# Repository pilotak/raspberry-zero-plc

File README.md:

# Raspberry Pi Zero/W based PLC
DIN mount PLC with following features
- power supply 7-45V DC
- 2x SPDT relay
- 1x SSR relay output (positive)
- 4x mosfet output (negative)
- 4x opto-isolated digital inputs with hardware debounce
- 3x analog input + 1 additional for power supply monitoring
- 1x CAN interface
- 1x RS232 (can be used for console or as standalone serial port)

## Picture

## BOM

| Qty | Component | Value | Package |
|:---:| --------- | ----- | ------- |
| 4 | Capacitor | 1uF/6.3V | C0805 |
| 2 | Capacitor | 10uF/6.3V | C0805 |
| 2 | Capacitor | 22p | C0805 |
| 12 | Capacitor | 100n | C0805 |
| 1 | Capacitor | 100uF/50V | PANASONIC_E |
| 1 | Capacitor | 470uF/10V | PANASONIC_E |
| 6 | Diode | S1B | DO214AC (SMA) |
| 1 | TVS | SMBJ33 | DO214AA (SMB) |
| 2 | Shottky diode| SS26 | DO214AA (SMB) |
| 1 | NAND Schmitt trigger | 74HC132D | SO14 |
| 1 | CAN controller | MCP2515-I/SO | SO-18L |
| 1 | RS232 driver | SP3222EET | SO-18L |
| 1 | CAN transceiver | TJA1050 | SO08 |
| 4 | Photocoupler | TLP185 | SOP04 |
| 1 | SSR relay | AQY212S | SOP04 |
| 2 | Realy | SRD-5VDC-SL-C | |
| 1 | Inductor | DE1207-100 | DR125 |
| 4 | N-mosfet | 2N7002 | SOT23 |
| 1 | Crystal | 16MHz | HC49U-V |
| 2 | PNP transistor | BCX71SMD | SOT23 |
| 1 | P-mosfet | DMG2305UX | SOT23 |
| 2 | N-mosfet | IRLML0060TRPBF | SOT23 |
| 5 | Resistor| 1K | R0805 |
| 5 | Resistor| 2K2 | R0805 |
| 4 | Resistor| 10K | R0805 |
| 1 | Resistor| 18K | R0805 |
| 3 | Resistor| 47K | R0805 |
| 4 | Resistor| 68K | R0805 |
| 6 | Resistor| 100K | R0805 |
| 1 | Resistor| 120R | R1206 |
| 4 | Resistor| 820K | R0805 |
| 1 | ADC | ADS1015 | module |
| 1 | LDO regulator | LM1117-3.3 | SOT223 |
| 1 | Step-down regulator | LM2576-5.0 | TO-263-5 |
| 1 | Raspberry Pi | Zero | |
| 2 | Screw terminal| KF301-5.0-2P | KF301-5.0-2P |
| 2 | Screw terminal| KF301-5.0-3P | KF301-5.0-3P |
| 7 | Screw terminal| KF350-3.5-2P | KF350-3.50-2P |
| 1 | DIN case | Z100J PS | |

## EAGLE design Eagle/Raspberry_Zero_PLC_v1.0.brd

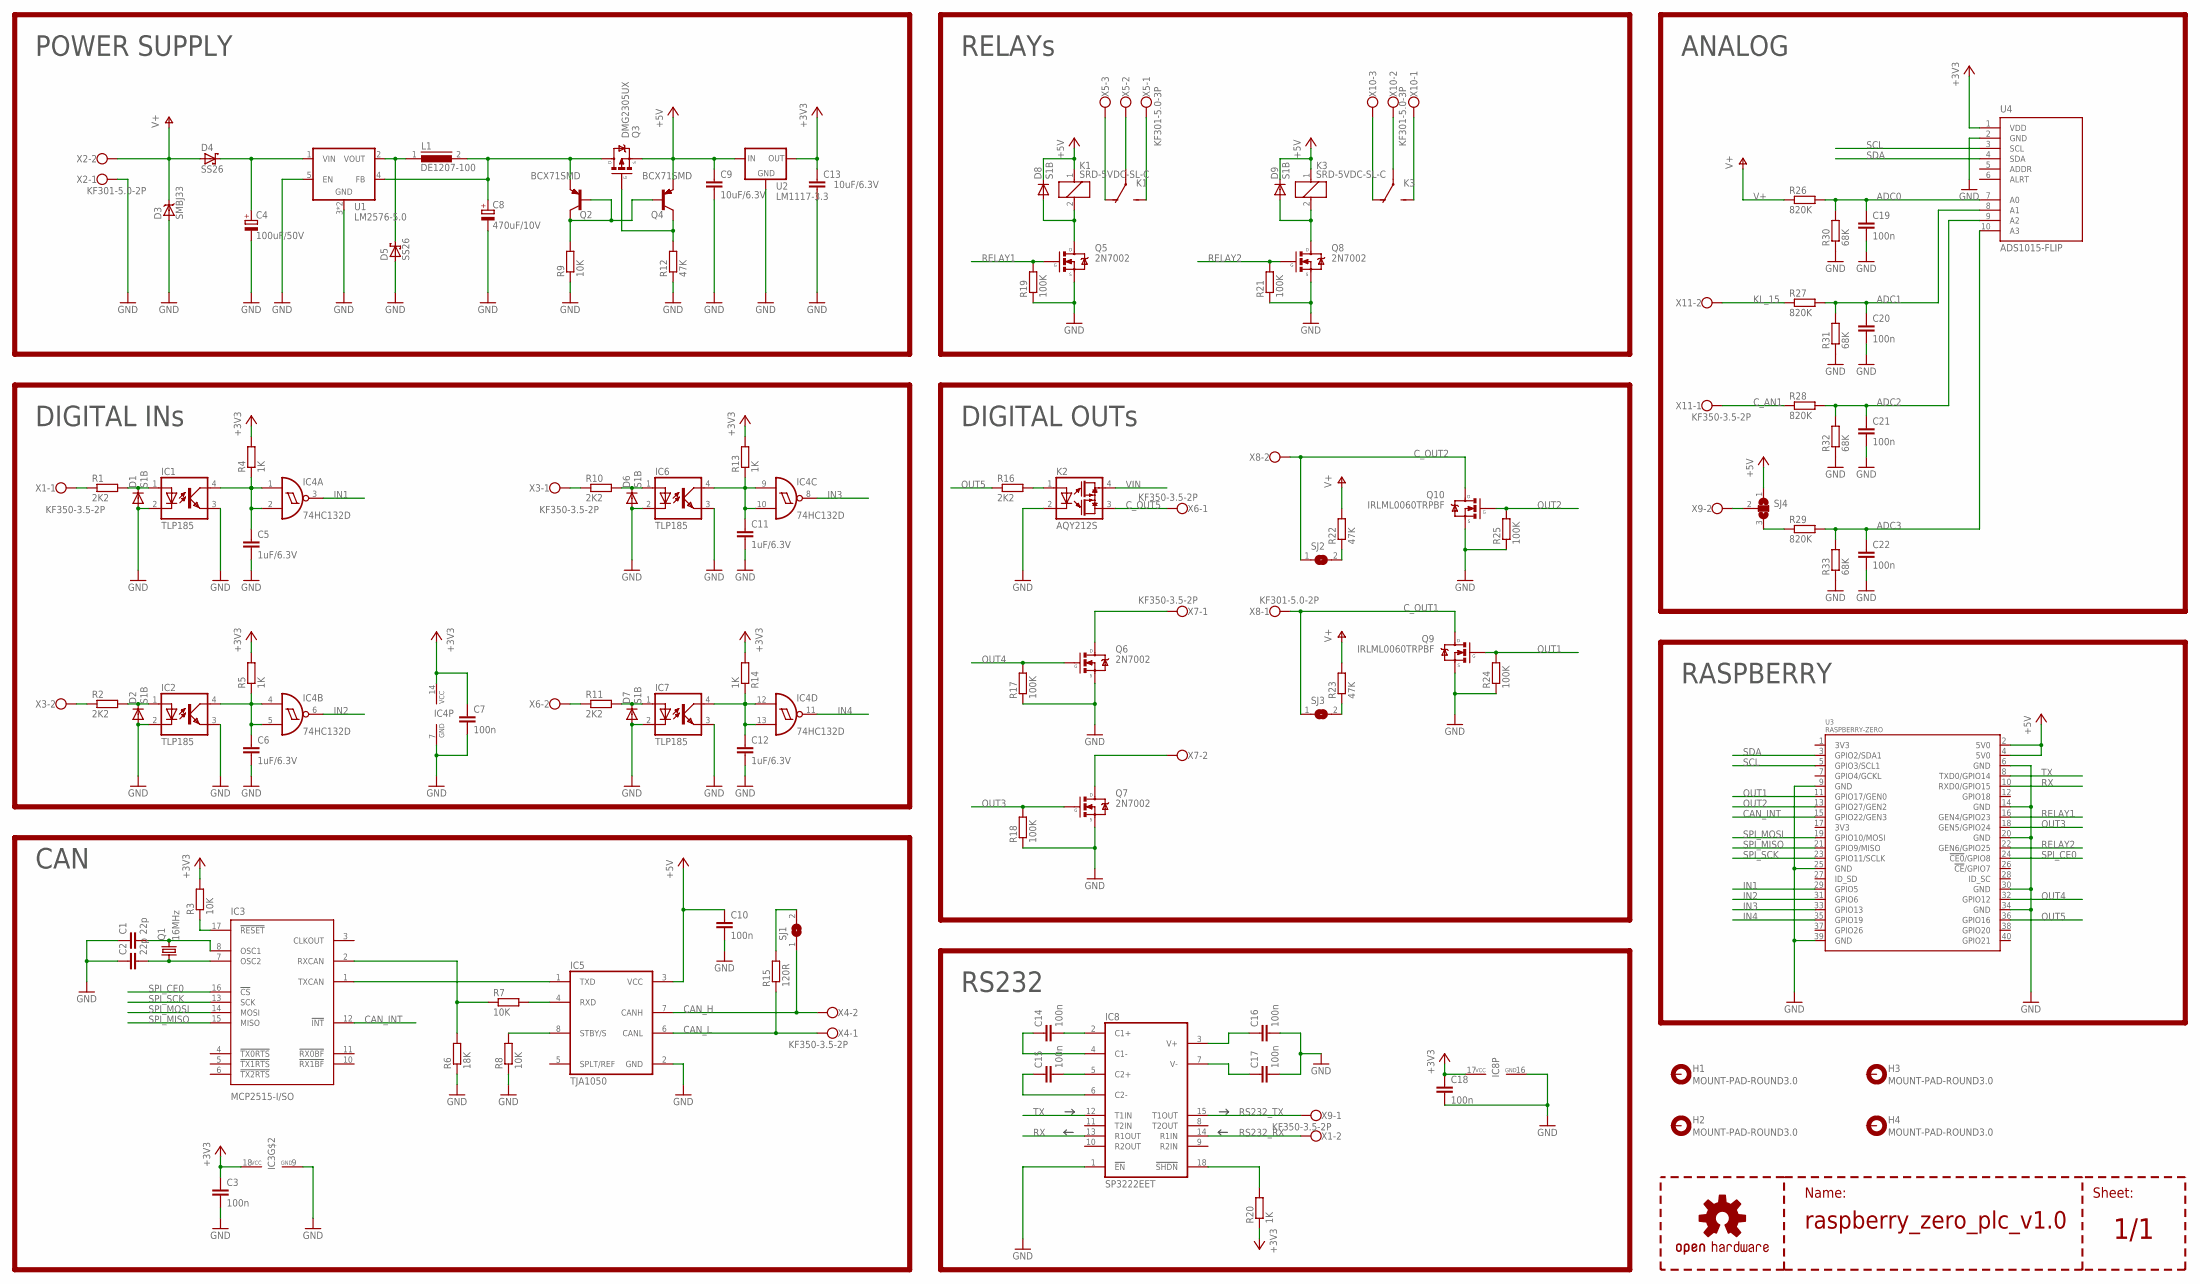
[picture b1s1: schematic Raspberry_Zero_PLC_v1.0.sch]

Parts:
C1, C2: 22p; C0805
C3, C7, C10, C14, C15, C16, C17, C18, C19, C20, C21, C22: 100n; C0805
C4: 100uF/50V; PANASONIC_E
C5, C6, C11, C12: 1uF/6.3V; C0805
C8: 470uF/10V; PANASONIC_E
C9, C13: 10uF/6.3V; C0805
D1, D2, D6, D7, D8, D9: S1B; DO214AC
D3: SMBJ33; DO214AA
D4, D5: SS26; DO214AA
H1, H2, H3, H4: MOUNT-PAD-ROUND3.0; 3,0-PAD
IC1, IC2, IC6, IC7: TLP185; SOP04
IC3: MCP2515-I/SO; SO-18L
IC4: 74HC132D; SO14
IC5: TJA1050; SO08
IC8: SP3222EET; SO-18L
K1, K3: SRD-5VDC-SL-C; SRD
K2: AQY212S; SOP04
L1: DE1207-100; DR125
LOGO1: OSHW-LOGOM-COPPER; OSHW-LOGO-M_COPPER
Q1: 16MHz; HC49U-V
Q2, Q4: BCX71SMD; SOT23
Q3: DMG2305UX; SOT23
Q5, Q6, Q7, Q8: 2N7002; SOT23
Q9, Q10: IRLML0060TRPBF; SOT23
R1, R2, R10, R11, R16: 2K2; R0805
R3, R7, R8, R9: 10K; R0805
R4, R5, R13, R14, R20: 1K; R0805
R6: 18K; R0805
R12, R22, R23: 47K; R0805
R15: 120R; R1206
R17, R18, R19, R21, R24, R25: 100K; R0805
R26, R27, R28, R29: 820K; R0805
R30, R31, R32, R33: 68K; R0805
SJ1, SJ2, SJ3: SJ
SJ4: SJ2W; SJ_2
U1: LM2576-5.0; TO-263-5
U2: LM1117-3.3; SOT223
U3: RASPBERRY-ZERO; RASPBERRYPI_ZERO
U4: ADS1015-FLIP; ADS1115-_FLIP
X1, X3, X4, X6, X7, X9, X11: KF350-3.5-2P; KF350-3.50-2P
X2, X8: KF301-5.0-2P
X5, X10: KF301-5.0-3P

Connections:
+3V3: C3.1, C7.1, C13.1, C18.1, IC3.18 (VCC), IC4.14 (VCC), IC8.17 (VCC), R3.2, R4.2, R5.2, R13.2, R14.2, R20.1, U2.2 (OUT), U2.4 (OUT), U4.1 (VDD)
+5V: C9.1, C10.1, D8.C, D9.C, IC5.3 (VCC), K1.1, K3.1, Q3.2 (S), Q4.2 (E), SJ4.1, U2.3 (IN), U3.2 (5V0), U3.4 (5V0)
ADC0: C19.1, R26.2, R30.2, U4.7 (A0)
ADC1: C20.1, R27.2, R31.2, U4.8 (A1)
ADC2: C21.1, R28.2, R32.2, U4.9 (A2)
ADC3: C22.1, R29.2, R33.2, U4.10 (A3)
CAN_H: IC5.7 (CANH), SJ1.1, X4.2
CAN_INT: IC3.12 (!INT!), U3.15 (GPIO22/GEN3)
CAN_L: IC5.6 (CANL), R15.1, X4.1
C_AN1: R28.1, X11.1
C_AN2/5V: SJ4.2, X9.2
C_IN1: R1.1, X1.1
C_IN2: R2.1, X3.2
C_IN3: R10.1, X3.1
C_IN4: R11.1, X6.2
C_OUT1: Q9.3 (D), SJ3.1, X8.1
C_OUT2: Q10.3 (D), SJ2.1, X8.2
C_OUT3: Q7.3 (D), X7.2
C_OUT4: Q6.3 (D), X7.1
C_OUT5: K2.3 (OUT0), X6.1
GND: C1.1, C2.1, C3.2, C4.-, C5.2, C6.2, C7.2, C8.-, C9.2, C10.2, C11.2, C12.2, C13.2, C16.2, C17.2, C18.2, C19.2, C20.2, C21.2, C22.2, D1.A, D2.A, D3.A, D5.A, D6.A, D7.A, IC1.2 (C), IC1.3 (EMIT), IC2.2 (C), IC2.3 (EMIT), IC3.9 (GND), IC4.7 (GND), IC5.2 (GND), IC6.2 (C), IC6.3 (EMIT), IC7.2 (C), IC7.3 (EMIT), IC8.1 (!EN!), IC8.16 (GND), K2.2 (C), Q5.2 (S), Q6.2 (S), Q7.2 (S), Q8.2 (S), Q9.2 (S), Q10.2 (S), R6.1, R8.1, R9.1, R12.1, R17.1, R18.1, R19.1, R21.1, R24.1, R25.1, R30.1, R31.1, R32.1, R33.1, U1.3 (GND), U1.5 (EN), U1.6 (GND), U2.1 (GND), U3.6 (GND), U3.9 (GND), U3.14 (GND), U3.20 (GND), U3.25 (GND), U3.30 (GND), U3.34 (GND), U3.39 (GND), U4.2 (GND), X2.1
IN1: IC4.3 (O), U3.29 (GPIO5)
IN2: IC4.6 (O), U3.31 (GPIO6)
IN3: IC4.8 (O), U3.33 (GPIO13)
IN4: IC4.11 (O), U3.35 (GPIO19)
KL_15: R27.1, X11.2
unnamed: Q2.1 (B), Q2.3 (C), Q4.1 (B), R9.2
unnamed: Q3.1 (G), Q4.3 (C), R12.2
unnamed: C2.2, IC3.7 (OSC2), Q1.1
unnamed: C8.+, L1.2, Q2.2 (E), Q3.3 (D), U1.4 (FB)
unnamed: C1.2, IC3.8 (OSC1), Q1.2
unnamed: IC3.1 (TXCAN), IC5.1 (TXD)
unnamed: IC3.2 (RXCAN), R6.2, R7.1
unnamed: IC5.8 (STBY/S), R8.2
unnamed: D5.C, L1.1, U1.2 (VOUT)
unnamed: IC5.4 (RXD), R7.2
unnamed: IC3.17 (!RESET!), R3.1
unnamed: D6.C, IC6.1 (A), R10.2
unnamed: C16.1, IC8.3 (V+)
unnamed: C17.1, IC8.7 (V-)
unnamed: D9.A, K3.2, Q8.3 (D)
unnamed: D8.A, K1.2, Q5.3 (D)
unnamed: C15.2, IC8.5 (C2+)
unnamed: C15.1, IC8.6 (C2-)
unnamed: C14.1, IC8.4 (C1-)
unnamed: C14.2, IC8.2 (C1+)
unnamed: R29.1, SJ4.3
unnamed: D1.C, IC1.1 (A), R1.2
unnamed: D2.C, IC2.1 (A), R2.2
unnamed: R22.1, SJ2.2
unnamed: R23.1, SJ3.2
unnamed: K2.1 (A), R16.2
unnamed: C5.1, IC1.4 (COL), IC4.1 (I0), IC4.2 (I1), R4.1
unnamed: C11.1, IC4.9 (I0), IC4.10 (I1), IC6.4 (COL), R13.1
unnamed: C6.1, IC2.4 (COL), IC4.4 (I0), IC4.5 (I1), R5.1
unnamed: C12.1, IC4.12 (I0), IC4.13 (I1), IC7.4 (COL), R14.1
unnamed: R15.2, SJ1.2
unnamed: IC8.18 (!SHDN!), R20.2
unnamed: D7.C, IC7.1 (A), R11.2
OUT1: Q9.1 (G), R24.2, U3.11 (GPIO17/GEN0)
OUT2: Q10.1 (G), R25.2, U3.13 (GPIO27/GEN2)
OUT3: Q7.1 (G), R18.2, U3.18 (GEN5/GPIO24)
OUT4: Q6.1 (G), R17.2, U3.32 (GPIO12)
OUT5: R16.1, U3.36 (GPIO16)
RELAY1: Q5.1 (G), R19.2, U3.16 (GEN4/GPIO23)
RELAY1_COM: K1.COM, X5.2
RELAY1_NC: K1.NC, X5.3
RELAY1_NO: K1.NO, X5.1
RELAY2: Q8.1 (G), R21.2, U3.22 (GEN6/GPIO25)
RELAY2_COM: K3.COM, X10.2
RELAY2_NC: K3.NC, X10.3
RELAY2_NO: K3.NO, X10.1
RS232_RX: IC8.14 (R1IN), X1.2
RS232_TX: IC8.15 (T1OUT), X9.1
RX: IC8.13 (R1OUT), U3.10 (RXD0/GPIO15)
SCL: U3.5 (GPIO3/SCL1), U4.3 (SCL)
SDA: U3.3 (GPIO2/SDA1), U4.4 (SDA)
SPI_CE0: IC3.16 (!CS!), U3.24 (!CE0!/GPIO8)
SPI_MISO: IC3.15 (MISO), U3.21 (GPIO9/MISO)
SPI_MOSI: IC3.14 (MOSI), U3.19 (GPIO10/MOSI)
SPI_SCK: IC3.13 (SCK), U3.23 (GPIO11/SCLK)
TX: IC8.12 (T1IN), U3.8 (TXD0/GPIO14)
V+: D3.C, D4.A, R22.2, R23.2, R26.1, X2.2
VIN: C4.+, D4.C, K2.4 (OUT1), U1.1 (VIN)

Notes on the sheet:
DIGITAL INs
DIGITAL OUTs
ANALOG
RS232
RASPBERRY
POWER SUPPLY
CAN
RELAYs
Sheet:
Name:

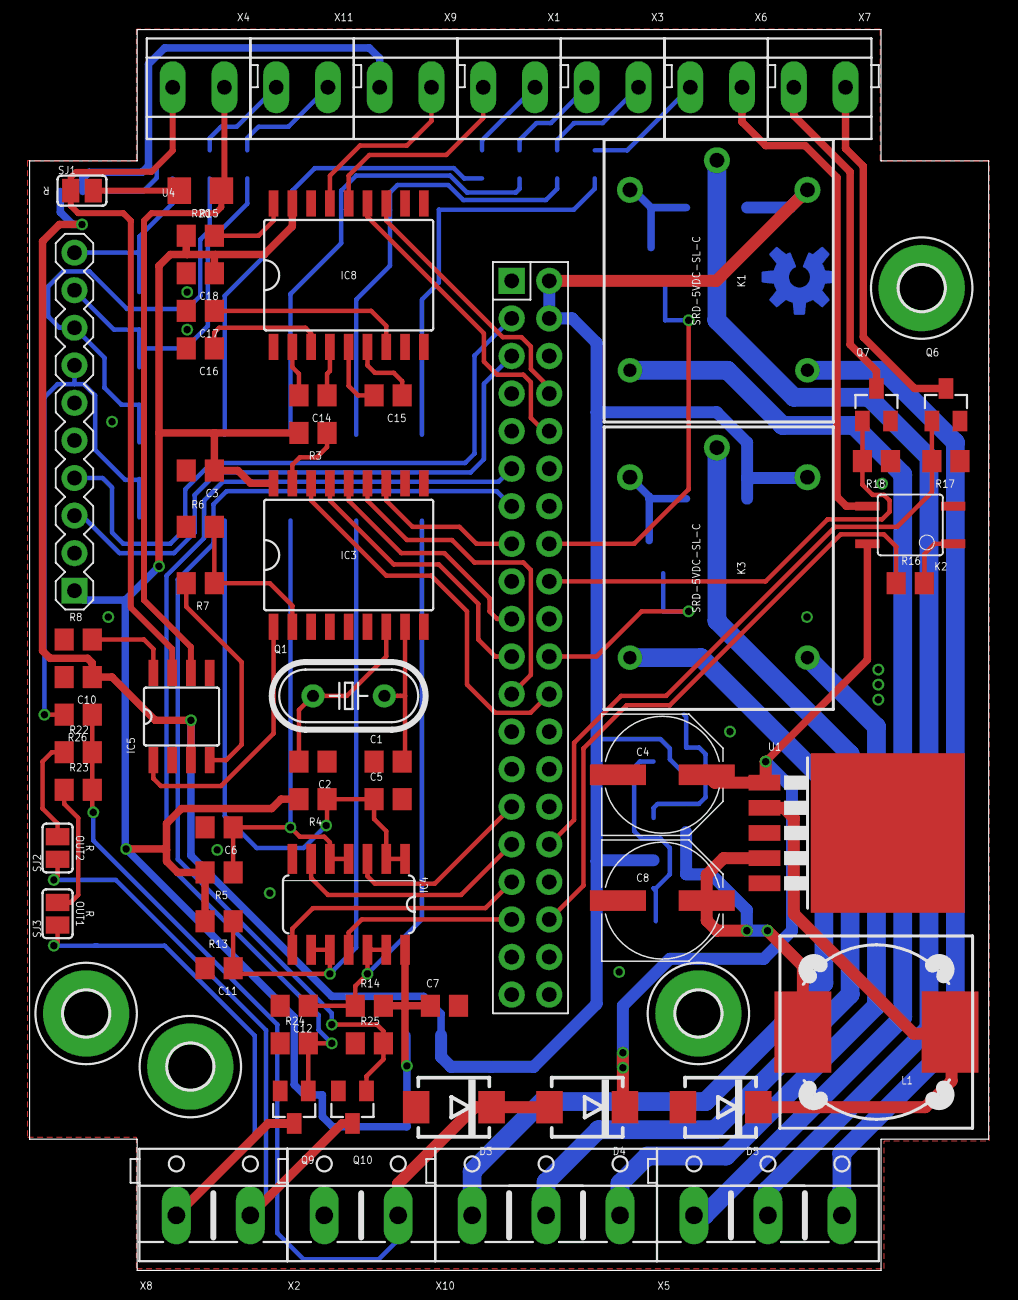
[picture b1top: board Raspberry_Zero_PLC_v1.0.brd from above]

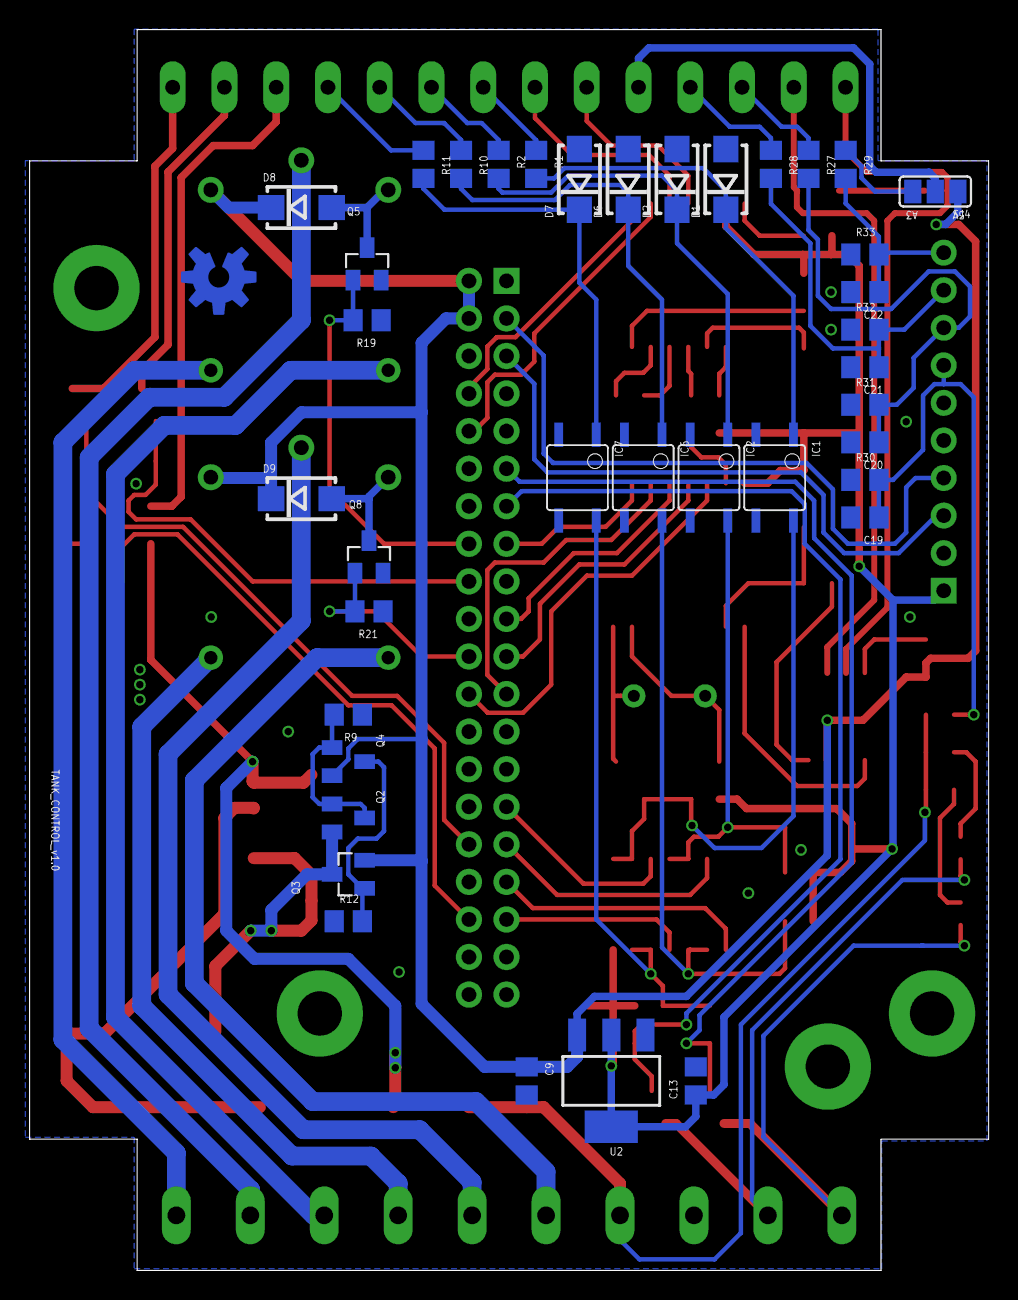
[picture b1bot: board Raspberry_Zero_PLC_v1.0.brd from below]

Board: 2 copper layers, 64.9 x 83.9 mm, 110 parts (39 on the bottom side), 84 nets.

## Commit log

2018-11-30 init
2018-11-30 files

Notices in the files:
parts and their libraries:
SparkFun-Aesthetics: Licensing: Creative Commons ShareAlike 4.0 International - https://creativecommons.org/licenses/by-sa/4.0
